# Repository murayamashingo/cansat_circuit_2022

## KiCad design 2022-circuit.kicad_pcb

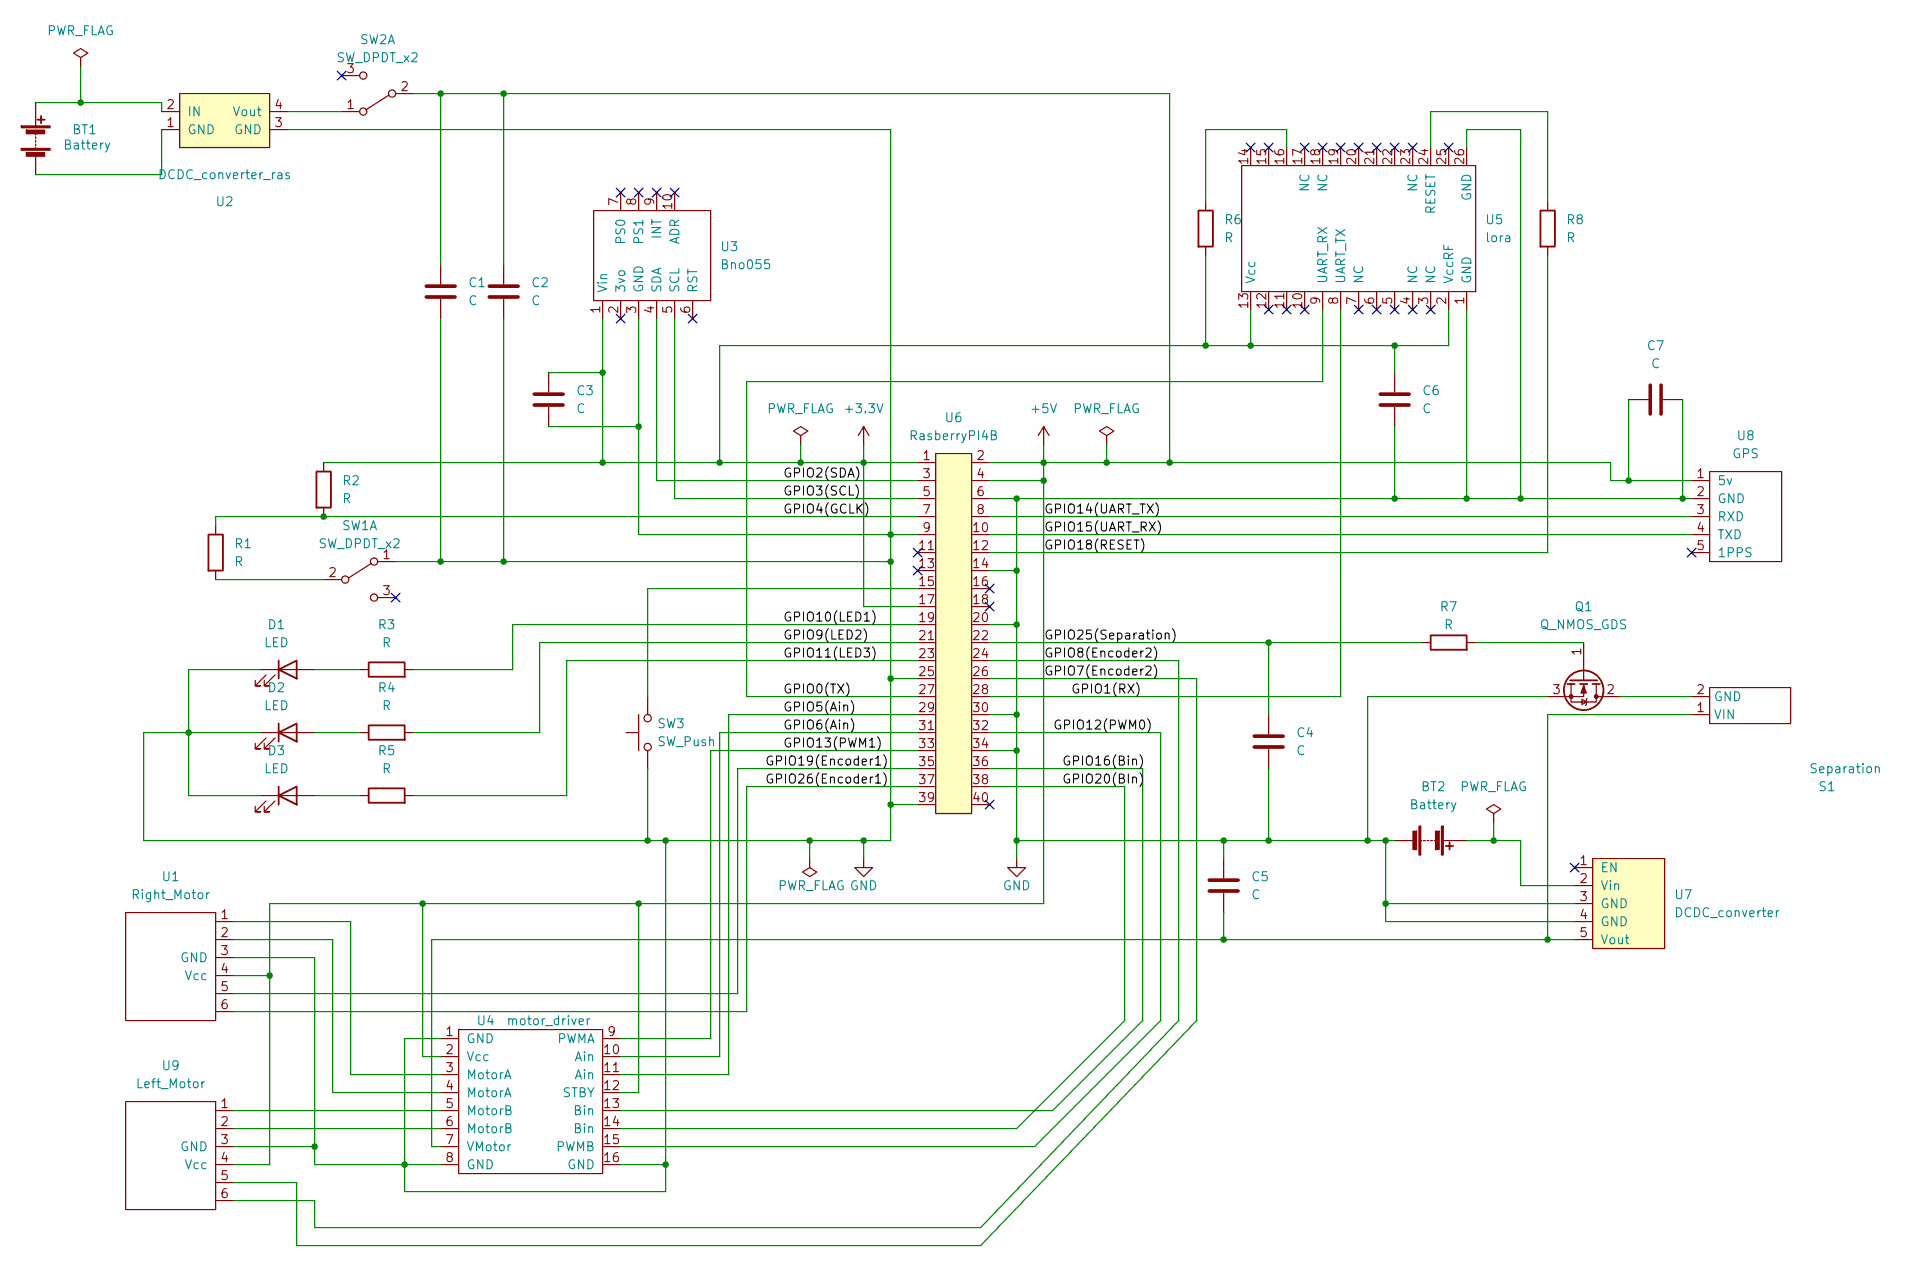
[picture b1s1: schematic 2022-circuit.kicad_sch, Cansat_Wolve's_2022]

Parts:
BT1, BT2: Battery; BT2_Motor
C1, C2, C3, C4, C5, C6, C7: C; CP_Radial_D5.0mm_P2.50mm
D1, D2, D3: LED; LED_D5.0mm
Q1: Q_NMOS_GDS; MOS_FET
R1, R2, R3, R4, R5, R6, R7, R8: R; R_Axial_DIN0207_L6.3mm_D2.5mm_P10.16mm_Horizontal
S1: Separation; separation
SW1, SW2: SW_DPDT_x2; PinSocket_1x03_P2.54mm_Vertical
SW3: SW_Push; Push_Button
U1: Right_Motor; Motor
U2: DCDC_converter_ras; DCDC_converter_ras_2022
U3: Bno055
U4: motor_driver
U5: lora; LoRa
U6: RasberryPI4B; raspberrypi
U7: DCDC_converter; DCDC_converter_servo
U8: GPS
U9: Left_Motor; Motor

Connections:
+3V3: C3.1, C6.1, R2.1, R6.2, U3.1 (Vin), U5.2 (VccRF), U5.13 (Vcc), U6.1, U6.17
/GPIO0(TX): U5.9 (UART_RX), U6.27
/GPIO1(RX): U5.8 (UART_TX), U6.28
/GPIO2(SDA): U3.4 (SDA), U6.3
/GPIO3(SCL): U3.5 (SCL), U6.5
/GPIO4(GCLK): R1.1, R2.2, U6.7
/GPIO5(Ain): U4.11 (Ain), U6.29
/GPIO6(Ain): U4.10 (Ain), U6.31
/GPIO9(LED2): R4.2, U6.21
/GPIO10(LED1): R3.2, U6.19
/GPIO11(LED3): R5.2, U6.23
/GPIO12(PWM0): U4.15 (PWMB), U6.32
/GPIO13(PWM1): U4.9 (PWMA), U6.33
/GPIO16(Bin): U4.13 (Bin), U6.36
/GPIO19(Encoder1): U1.5, U6.35
/GPIO20(BIn): U4.14 (Bin), U6.38
/GPIO26(Encoder1): U1.6, U6.37
GND: BT2.2 (-), C1.2, C2.2, C3.2, C4.2, C5.1, C6.2, C7.2, D1.1 (K), D2.1 (K), D3.1 (K), Q1.3 (S), SW1.1 (A), SW3.1, U1.3 (GND), U2.3 (GND), U3.3 (GND), U4.1 (GND), U4.8 (GND), U4.16 (GND), U5.1 (GND), U5.26 (GND), U6.6, U6.9, U6.14, U6.20, U6.25, U6.30, U6.34, U6.39, U7.3 (GND), U7.4 (GND), U8.2 (GND~), U9.3 (GND)
unnamed: BT1.1 (+), U2.2 (IN)
unnamed: BT1.2 (-), U2.1 (GND)
unnamed: BT2.1 (+), U7.2 (Vin)
unnamed: C5.2, S1.1 (VIN), U4.7 (VMotor), U7.5 (Vout)
unnamed: D1.2 (A), R3.1
unnamed: D2.2 (A), R4.1
unnamed: D3.2 (A), R5.1
unnamed: Q1.1 (G), R7.2
unnamed: Q1.2 (D), S1.2 (GND)
unnamed: R1.2, SW1.2 (B)
unnamed: R6.1, U5.16
unnamed: R8.1, U5.24 (RESET)
unnamed: SW2.1 (A), U2.4 (Vout)
unnamed: SW3.2, U6.15
unnamed: U1.1, U4.3 (MotorA)
unnamed: U1.2, U4.4 (MotorA)
unnamed: U4.5 (MotorB), U9.1
unnamed: U4.6 (MotorB), U9.2

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
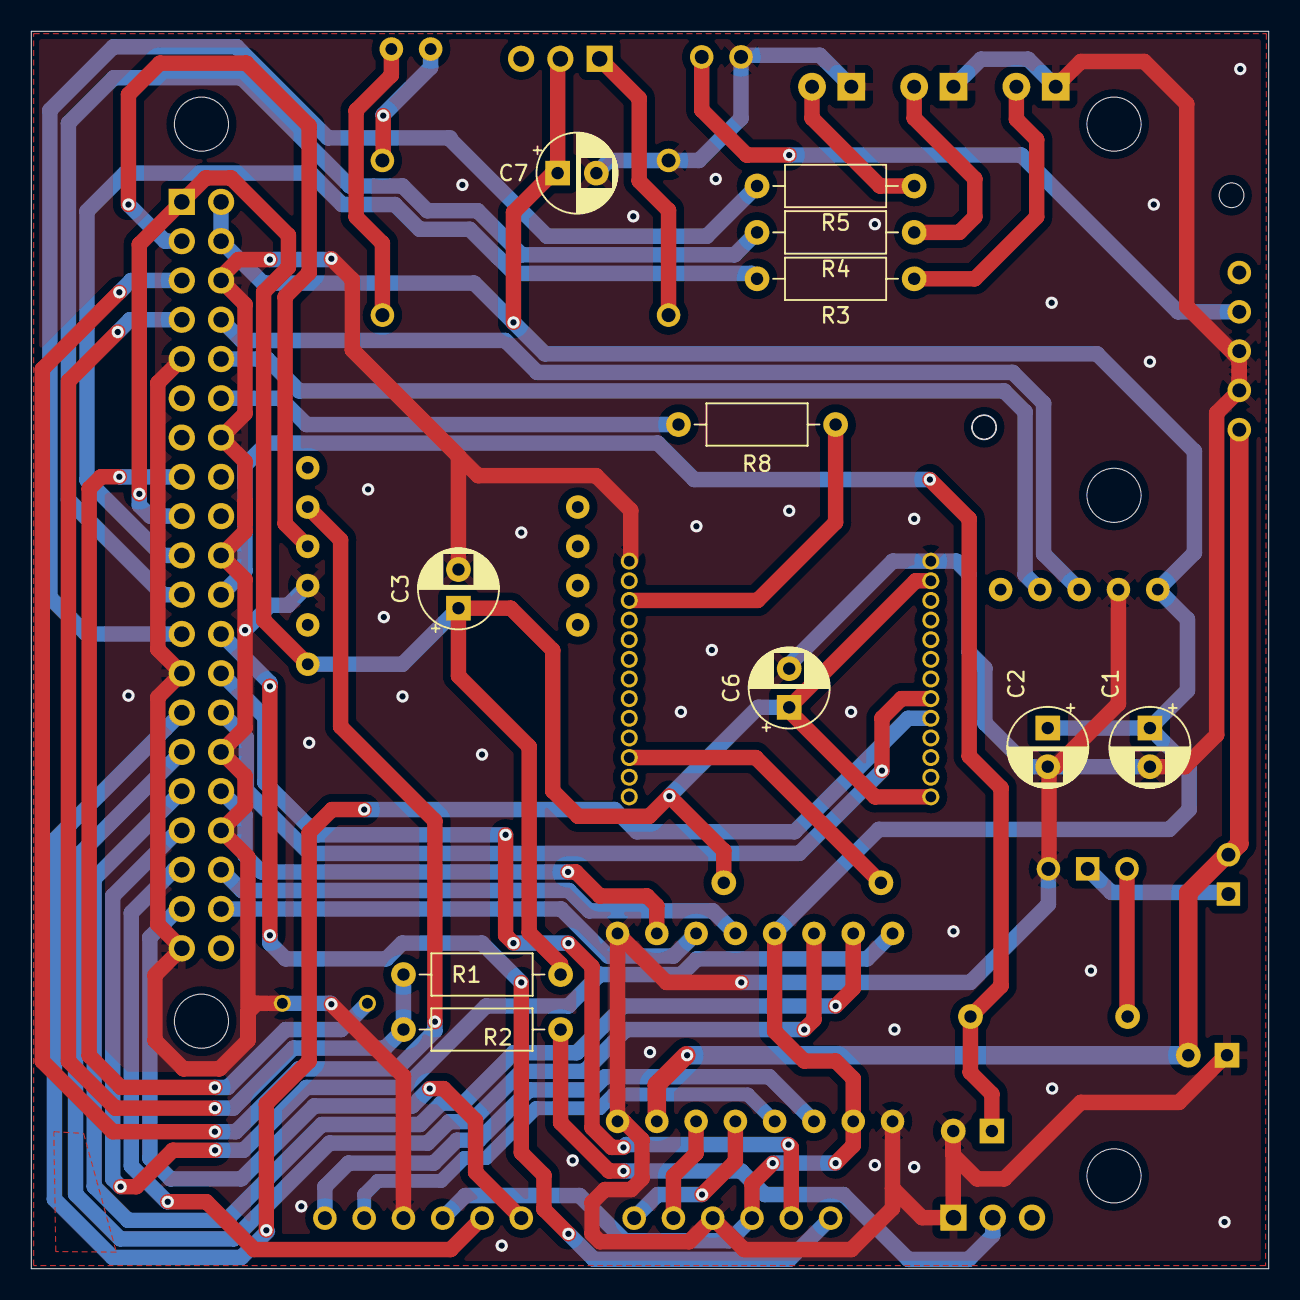
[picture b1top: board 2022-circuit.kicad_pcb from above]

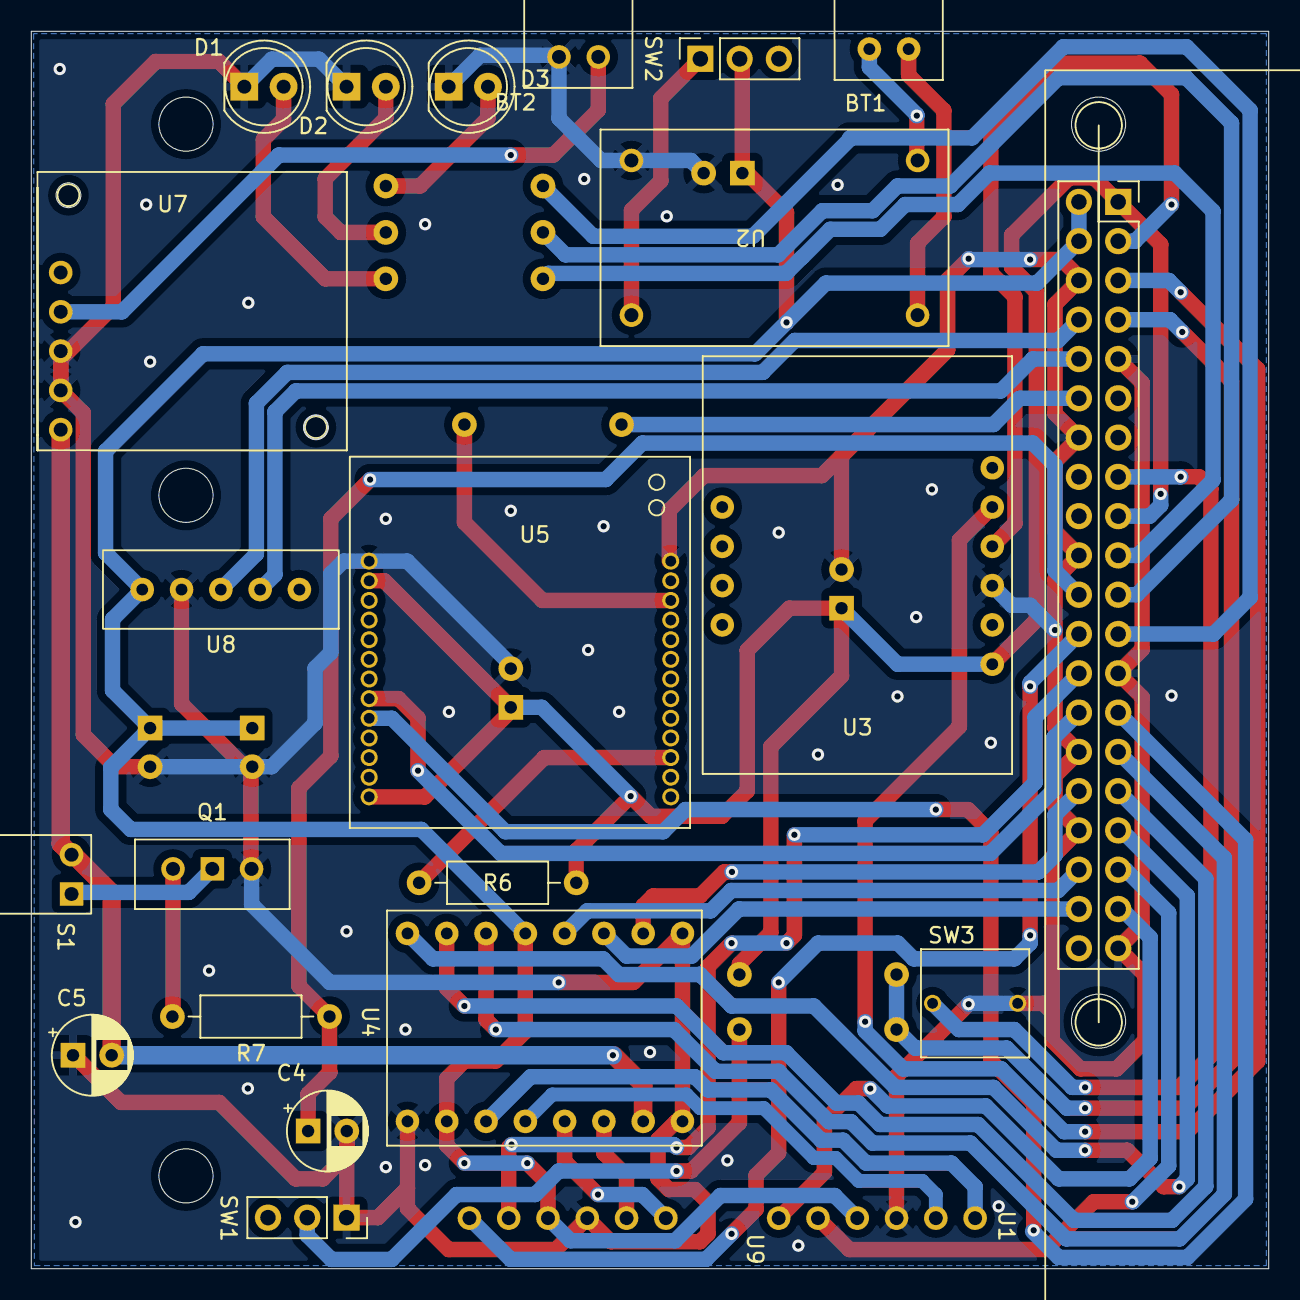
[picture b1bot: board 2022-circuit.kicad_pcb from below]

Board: 2 copper layers, 80.0 x 80.0 mm, 34 parts (23 on the bottom side), 43 nets.

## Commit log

2024-02-05 feat:1st
